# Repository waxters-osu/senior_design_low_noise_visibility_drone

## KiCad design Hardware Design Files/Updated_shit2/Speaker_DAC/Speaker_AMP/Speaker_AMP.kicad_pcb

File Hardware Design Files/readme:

This folder is for all hardware design files.

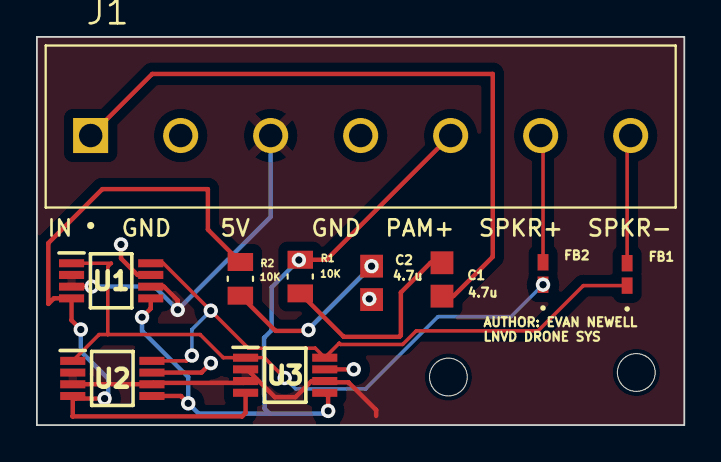
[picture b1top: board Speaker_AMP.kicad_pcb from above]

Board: 2 copper layers, 36.0 x 21.6 mm, 12 parts (0 on the bottom side), 11 nets.

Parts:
C1, C2: 4.7u; Cap0805
FB1, FB2: FerriteBead; IND_BLM15_0402_MUR-M
H1, H2: MountingHole; MountingHole_2.1mm
J1: IN GND 5V GND PAM+ SPKR+ SPKR-; CUI_TB001-500-07BE
R1, R2: 10K; RESC2012X60N
U1, U2, U3: PAM8304; SOP65P490X110-8N

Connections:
/5V: J1.3, U1.2 (PVDD), U1.3 (VDD), U1.6 (SD_N), U2.2 (PVDD), U2.3 (VDD), U2.6 (SD_N), U3.2 (PVDD), U3.3 (VDD), U3.6 (SD_N)
/PAM_NEG: R2.2, U1.4 (IN-), U2.4 (IN-), U3.4 (IN-)
/PAM_O+: FB2.1, U1.1 (OUT+), U2.1 (OUT+), U3.1 (OUT+)
/PAM_O-: FB1.1, U1.8 (OUT-), U2.8 (OUT-), U3.8 (OUT-)
/PAM_POS: J1.5, R1.2, U1.5 (IN+), U2.5 (IN+), U3.5 (IN+)
/SNGL_IN: C1.1, J1.1
/SPEAKER+: FB2.2, J1.6
/SPEAKER-: FB1.2, J1.7
GND: C2.1, J1.2, J1.4, U1.7 (GND), U2.7 (GND), U3.7 (GND)
unnamed: C1.2, R1.1
unnamed: C2.2, R2.1

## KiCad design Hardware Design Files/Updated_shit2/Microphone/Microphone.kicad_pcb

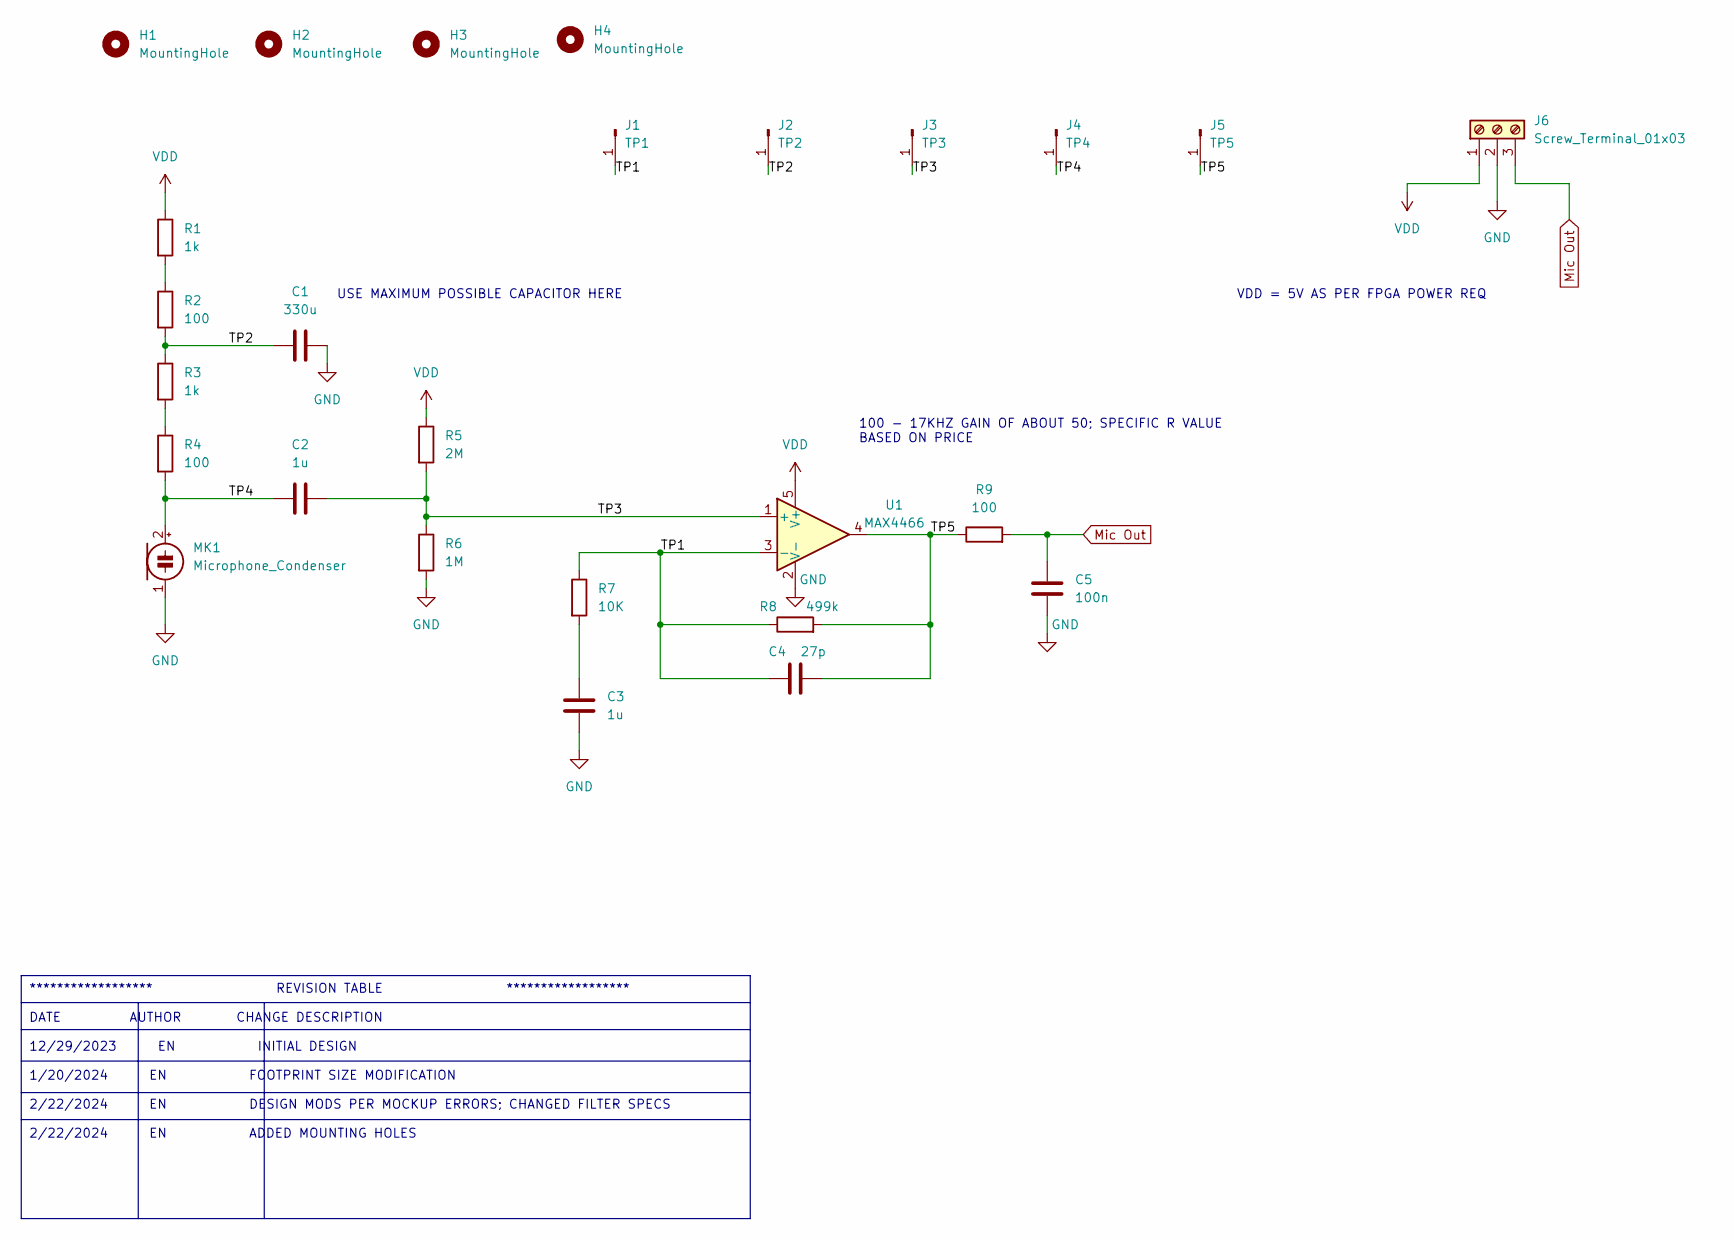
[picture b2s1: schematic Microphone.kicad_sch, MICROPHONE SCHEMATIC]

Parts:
C1: 330u; CAPC3225X280N; Digikey Part # GRM32EC80E337ME05K
C2, C3: 1u; Cap0805; Digikey Part # CL21B105KAFNNNE
C4: 27p; Cap0805; Digikey Part # C0805C270K5GAC7800
C5: 100n; Cap0805; Digikey Part # CC0805KRX7R9BB104
H1, H2, H3, H4: MountingHole; MountingHole_3mm
J1: TP1; ADAM-TECH_PH1-01-UA; Digikey Part # PH1-01-UA
J2: TP2; ADAM-TECH_PH1-01-UA; Digikey Part # PH1-01-UA
J3: TP3; ADAM-TECH_PH1-01-UA; Digikey Part # PH1-01-UA
J4: TP4; ADAM-TECH_PH1-01-UA; Digikey Part # PH1-01-UA
J5: TP5; ADAM-TECH_PH1-01-UA; Digikey Part # PH1-01-UA
J6: Screw_Terminal_01x03; CONN_1984976_PXC; Digikey Part # 1984976
MK1: Microphone_Condenser; CMA_CUI_9P7X9P7_CUD; Digikey Part # CMA-6524PF
R1, R3: 1k; RESC2012X60N; Digikey Part # RMCF0805FT1K00
R2, R4, R9: 100; RESC2012X60N; Digikey Part # RC0805FR-07100RL
R5: 2M; RESC2012X60N; Digikey Part # CRCW08052M00FKECC
R6: 1M; RESC2012X60N; Digikey Part # RMCF0805FG1M00
R7: 10K; RESC2012X60N; Digikey Part # RMCF0805FT10K0
R8: 499k; RESC2012X60N; Digikey Part # CR0805-FX-4993ELF
U1: MAX4466; Mic_Op_Amp; Digikey Part # MAX4466EXK+T

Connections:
/TP1: C4.1, J1.1, R7.1, R8.1, U1.3 (-)
/TP2: C1.1, J2.1, R2.2, R3.1
/TP3: C2.2, J3.1, R5.2, R6.1, U1.1 (+)
/TP4: C2.1, J4.1, MK1.2 (+), R4.2
/TP5: C4.2, J5.1, R8.2, R9.1, U1.4
GND: C1.2, C3.2, C5.2, J6.2, MK1.1 (-), R6.2, U1.2 (V-)
Mic Out: C5.1, J6.3, R9.2
unnamed: C3.1, R7.2
unnamed: R1.2, R2.1
unnamed: R3.2, R4.1
VDD: J6.1, R1.1, R5.1, U1.5 (V+)

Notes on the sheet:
****************** REVISION TABLE ****************** DATE AUTHOR CHANGE DESCRIPTION 12/29/2023 EN INITIAL DESIGN 1/20/2024 EN FOOTPRINT SIZE MODIFICATION 2/22/2024 EN DESIGN MODS PER MOCKUP ERRORS; CHANGED FILTER SPECS 2/22/2024 EN ADDED MOUNTING HOLES
VDD = 5V AS PER FPGA POWER REQ
100 - 17KHZ GAIN OF ABOUT 50; SPECIFIC R VALUE BASED ON PRICE
USE MAXIMUM POSSIBLE CAPACITOR HERE

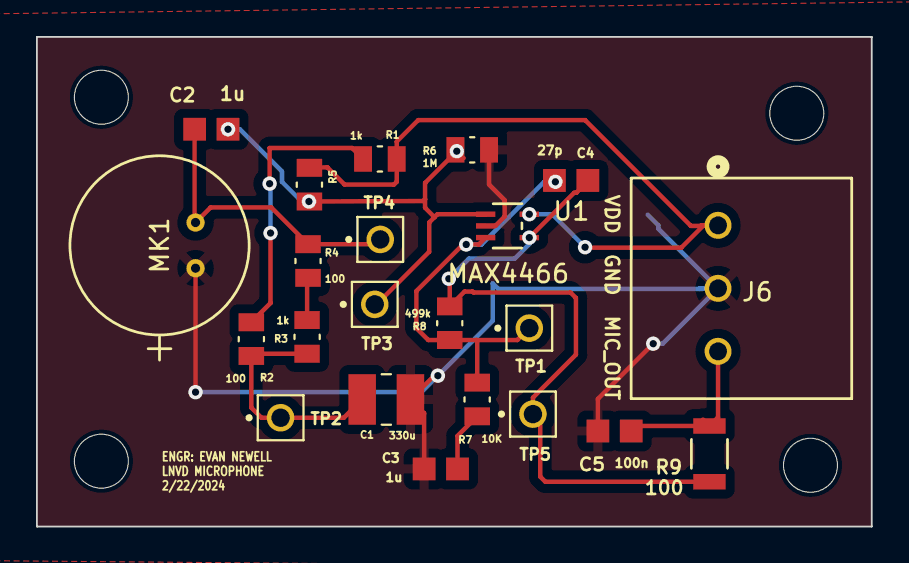
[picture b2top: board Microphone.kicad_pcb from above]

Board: 2 copper layers, 46.4 x 27.2 mm, 26 parts (0 on the bottom side), 11 nets.

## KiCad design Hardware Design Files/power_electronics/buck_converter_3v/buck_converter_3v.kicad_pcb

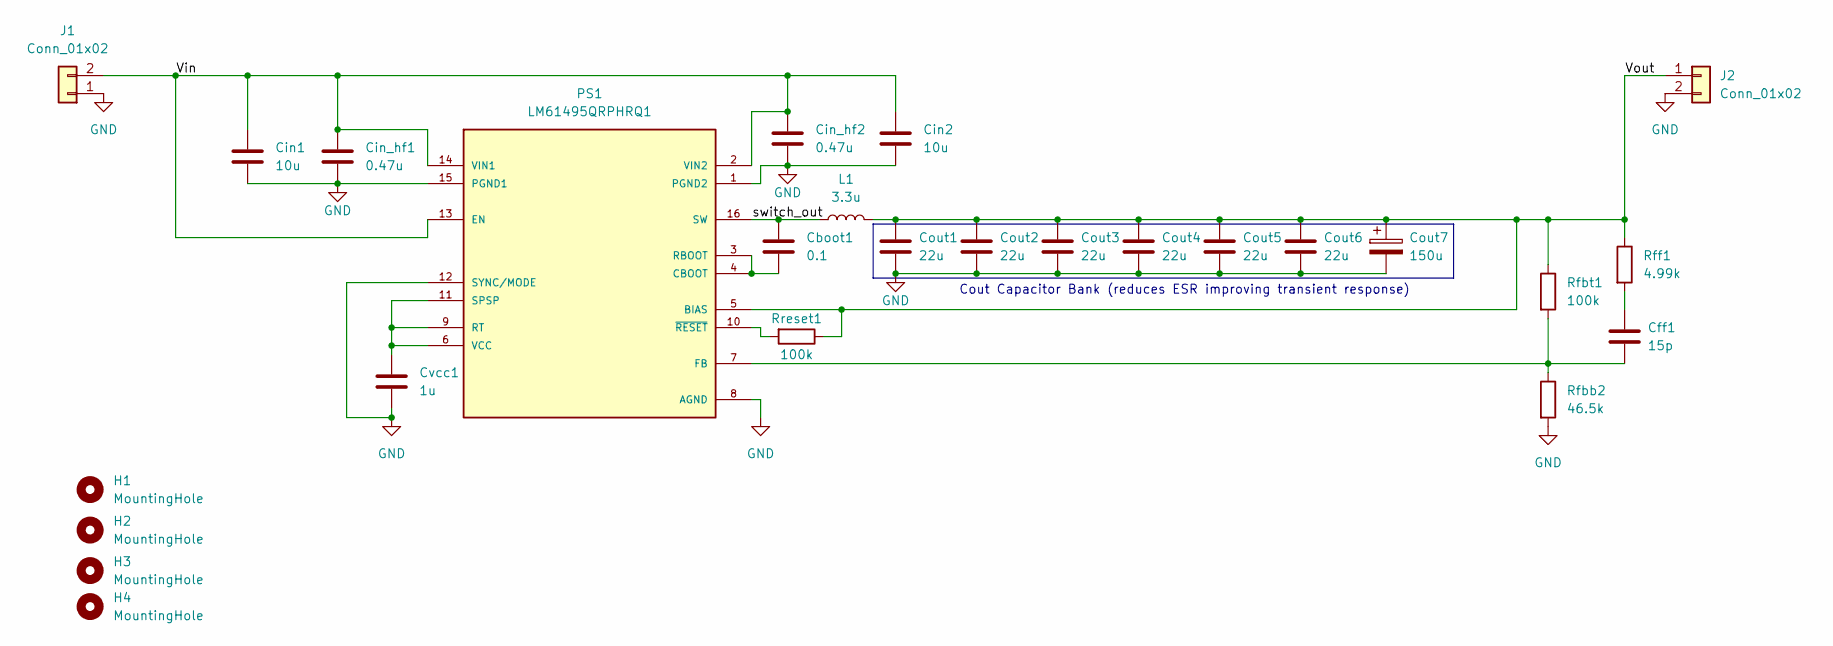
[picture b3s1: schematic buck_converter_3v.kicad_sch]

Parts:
Cboot1: 0.1; C_0805_2012Metric; Digikey PN CL21B104KACNNNC
Cff1: 15p; C_0805_2012Metric; Digikey PN CC0805JRNPO9BN150
Cin1, Cin2: 10u; C_1206_3216Metric; Digikey PN CL31B106KBHNNNE
Cin_hf1, Cin_hf2: 0.47u; C_0603_1608Metric; Digikey PN UMK107B7474KA-TR
Cout1, Cout2, Cout3, Cout4, Cout5, Cout6: 22u; C_0805_2012Metric; Digikey PN CL21A226MQQNNNE
Cout7: 150u; CP_Radial_D5.0mm_P2.00mm; DigikeyPN 860020272007
Cvcc1: 1u; C_0805_2012Metric; Digikey PN CL21B105KAFNNNE
H1, H2, H3, H4: MountingHole; MountingHole_2.5mm_Pad
J1, J2: Conn_01x02; 2-terminal-screw-connector-691137710002; Digikey PN 691137710002
L1: 3.3u; TMPC 1004H-3R3MG-D; Digikey PN TMPC 1004H-3R3MG-D
PS1: LM61495QRPHRQ1; CONV_LM61495QRPHRQ1; PARTREV 08/2018; Digikey PN LM61495QRPHRQ1
Rfbb2: 46.5k; R_0805_2012Metric; Digikey PN ERA-6AEB4642V
Rfbt1: 100k; R_0805_2012Metric; Digikey PN ERA-6AEB104V
Rff1: 4.99k; R_0805_2012Metric; Digikey PN ERA-6AEB4991V
Rreset1: 100k; R_0805_2012Metric; Digikey PN ERA-6AEB104V

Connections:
/Vin: Cin1.1, Cin2.1, Cin_hf1.1, Cin_hf2.1, J1.2, PS1.2 (VIN2), PS1.13 (EN), PS1.14 (VIN1)
/Vout: Cout1.1, Cout2.1, Cout3.1, Cout4.1, Cout5.1, Cout6.1, Cout7.1, J2.1, L1.2, PS1.5 (BIAS), Rfbt1.1, Rff1.1, Rreset1.1
/switch_out: Cboot1.1, L1.1, PS1.16 (SW)
GND: Cin1.2, Cin2.2, Cin_hf1.2, Cin_hf2.2, Cout1.2, Cout2.2, Cout3.2, Cout4.2, Cout5.2, Cout6.2, Cout7.2, Cvcc1.1, J1.1, J2.2, PS1.1 (PGND2), PS1.8 (AGND), PS1.12 (SYNC/MODE), PS1.15 (PGND1), Rfbb2.2; also elsewhere on the board
unnamed: Cff1.1, Rff1.2
unnamed: Cboot1.2, PS1.3 (RBOOT), PS1.4 (CBOOT)
unnamed 6: Cff1.2, PS1.7 (FB), Rfbb2.1, Rfbt1.2; also elsewhere on the board
unnamed: Cvcc1.2, PS1.6 (VCC), PS1.9 (RT), PS1.11 (SPSP)
unnamed: PS1.10 (~RESET), Rreset1.2

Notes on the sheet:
Cout Capacitor Bank (reduces ESR improving transient response)

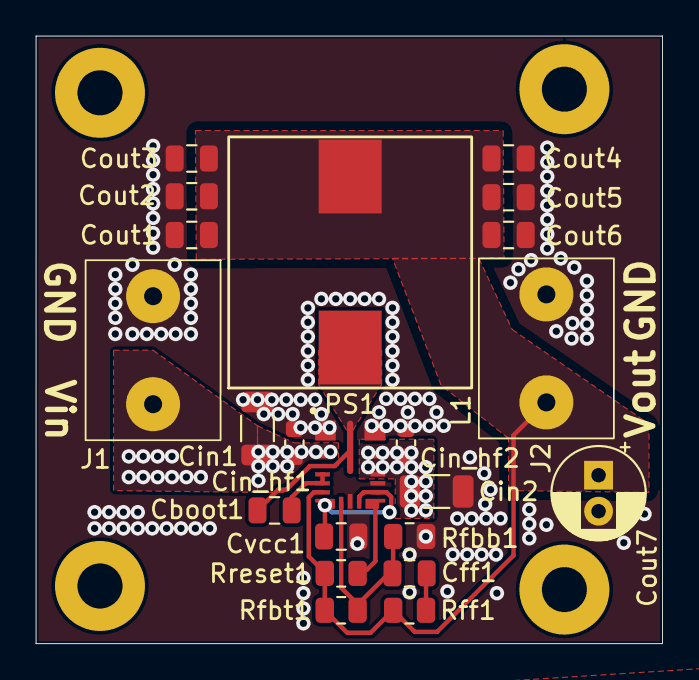
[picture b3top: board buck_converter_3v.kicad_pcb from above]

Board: 2 copper layers, 34.8 x 33.8 mm, 26 parts (0 on the bottom side), 9 nets.

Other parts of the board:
Rfbb1: 25.5k; R_0805_2012Metric

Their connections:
GND: Rfbb1.2; also elsewhere on the board
unnamed 6: Rfbb1.1; also elsewhere on the board

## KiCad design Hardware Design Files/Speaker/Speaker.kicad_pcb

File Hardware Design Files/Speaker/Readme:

This folder contains all hardware files pertaining to the speaker

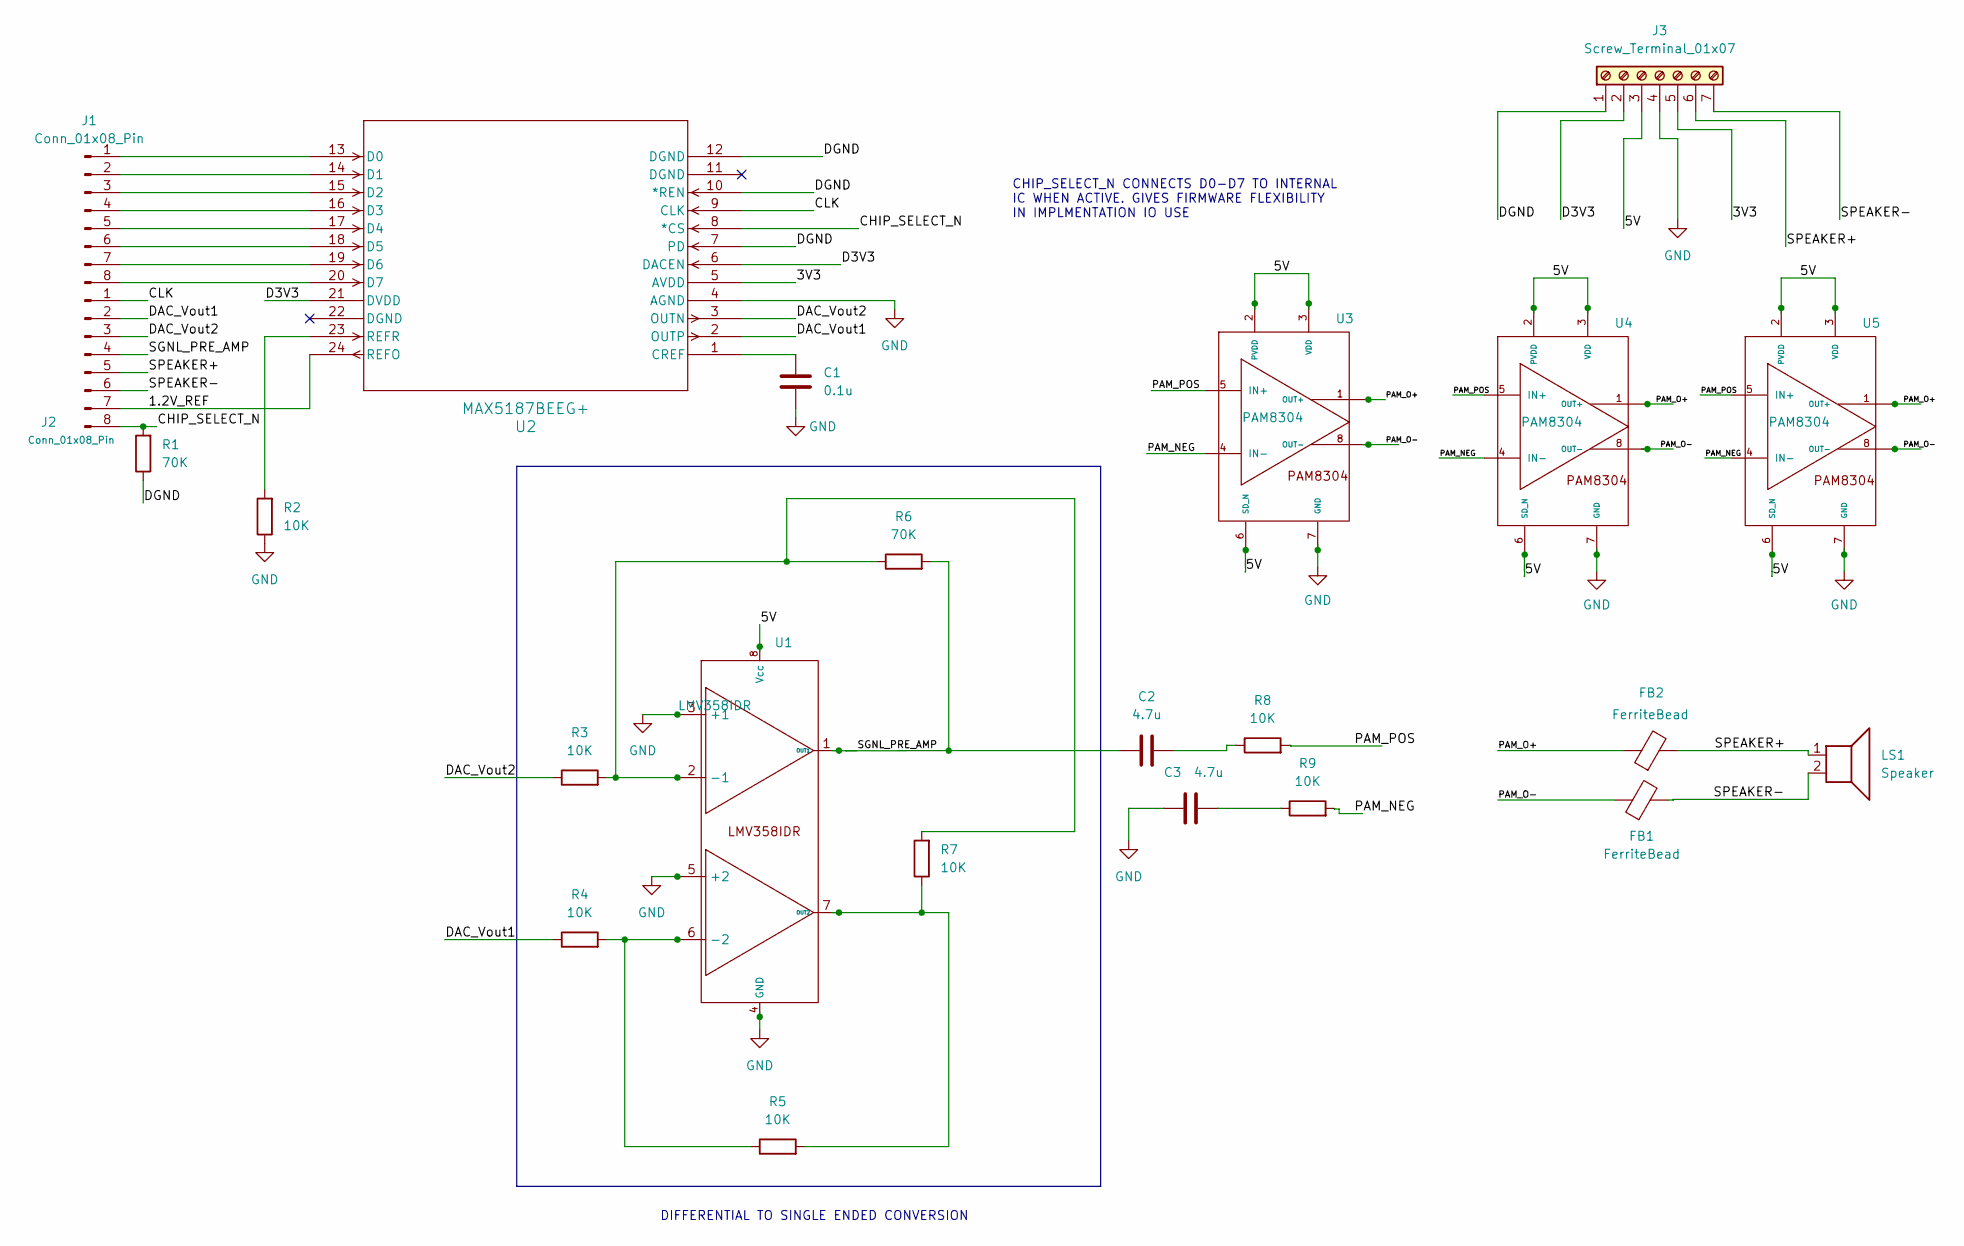
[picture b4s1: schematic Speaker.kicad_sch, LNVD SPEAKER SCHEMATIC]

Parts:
C1: 0.1u; CAP_CL10_SAM-M; DIGIKEY PART # GRM033C81E104ME14D
C2, C3: 4.7u; CAP_CL10_SAM-M; DIGIKEY PART # CL10A475KQ8NNWC
FB1, FB2: FerriteBead; IND_BLM15_0402_MUR-M; DIGIKEY PART # BLM15AG121SN1D
J1, J2: Conn_01x08_Pin; CONN_1945151_PXC; DIGIKEY PART # 1945151
J3: Screw_Terminal_01x07; CUI_TB001-500-07BE; DIGIKEY PART # TB001-500-07BE
LS1: Speaker; DIGIKEY PART # CDS-4224-84SP
R1, R6: 70K; RESC2012X60N; DIGIKEY PART # ERJ-1GNF6982C
R2, R3, R4, R5, R7, R8, R9: 10K; RESC2012X60N; DIGIKEY PART # RMCF0805FT10K0
U1: LMV358IDR; D8-M; DIGIKEY PART # LMV358IDR
U2: MAX5187BEEG+; 21-0055H_24-M; DIGIKEY PART # MAX5187BEEG+
U3, U4, U5: PAM8304; SOP65P490X110-8N; DIGIKEY PART # PAM8304ASR

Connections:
/1.2V_REF: J2.7, U2.24 (REFO)
/3V3: J3.5, U2.5 (AVDD)
/5V: J3.3, U1.8 (Vcc), U3.2 (PVDD), U3.3 (VDD), U3.6 (SD_N), U4.2 (PVDD), U4.3 (VDD), U4.6 (SD_N), U5.2 (PVDD), U5.3 (VDD), U5.6 (SD_N)
/CHIP_SELECT_N: J2.8, R1.2, U2.8 (*CS)
/CLK: J2.1, U2.9 (CLK)
/D3V3: J3.2, U2.6 (DACEN), U2.21 (DVDD)
/DAC_Vout1: J2.2, R4.1, U2.2 (OUTP)
/DAC_Vout2: J2.3, R3.1, U2.3 (OUTN)
/DGND: J3.1, R1.1, U2.7 (PD), U2.10 (*REN), U2.12 (DGND)
/PAM_NEG: R9.2, U3.4 (IN-), U4.4 (IN-), U5.4 (IN-)
/PAM_O+: FB2.1, U3.1 (OUT+), U4.1 (OUT+), U5.1 (OUT+)
/PAM_O-: FB1.1, U3.8 (OUT-), U4.8 (OUT-), U5.8 (OUT-)
/PAM_POS: R8.2, U3.5 (IN+), U4.5 (IN+), U5.5 (IN+)
/SGNL_PRE_AMP: C2.1, J2.4, R6.2, U1.1 (OUT1)
/SPEAKER+: FB2.2, J2.5, J3.6, LS1.1
/SPEAKER-: FB1.2, J2.6, J3.7, LS1.2
GND: C1.2, C3.1, J3.4, R2.1, U1.3 (+1), U1.4 (GND), U1.5 (+2), U2.4 (AGND), U3.7 (GND), U4.7 (GND), U5.7 (GND)
unnamed: C2.2, R8.1
unnamed: C3.2, R9.1
unnamed: J1.1, U2.13 (D0)
unnamed: J1.2, U2.14 (D1)
unnamed: J1.3, U2.15 (D2)
unnamed: J1.4, U2.16 (D3)
unnamed: J1.5, U2.17 (D4)
unnamed: J1.6, U2.18 (D5)
unnamed: J1.7, U2.19 (D6)
unnamed: J1.8, U2.20 (D7)
unnamed: R3.2, R6.1, R7.2, U1.2 (-1)
unnamed: R4.2, R5.1, U1.6 (-2)
unnamed: R5.2, R7.1, U1.7 (OUT2)
unnamed: C1.1, U2.1 (CREF)
unnamed: R2.2, U2.23 (REFR)

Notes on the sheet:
DIFFERENTIAL TO SINGLE ENDED CONVERSION
CHIP_SELECT_N CONNECTS D0-D7 TO INTERNAL IC WHEN ACTIVE. GIVES FIRMWARE FLEXIBILITY IN IMPLMENTATION IO USE

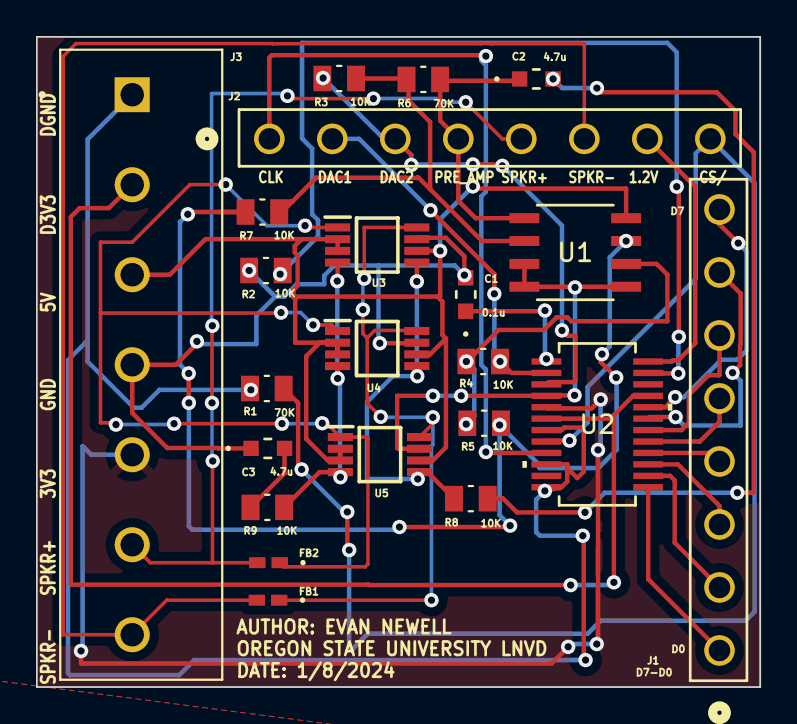
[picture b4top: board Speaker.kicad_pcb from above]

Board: 2 copper layers, 40.2 x 36.1 mm, 22 parts (0 on the bottom side), 32 nets.

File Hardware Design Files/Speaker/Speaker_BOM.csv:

"Reference","Value","Footprint","Datasheet","DIGIKEY PART #","PRICE","Qty"
"C1","0.1u","Footprints:CAP_CL10_SAM-M","~https://search.murata.co.jp/Ceramy/image/img/A01X/G101/ENG/G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","GRM033C81E104ME14D","$0.10","1"
"C2, C3","4.7u","Footprints:CAP_CL10_SAM-M","~https://mm.digikey.com/Volume0/opasdata/d220001/medias/docus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","CL10A475KQ8NNWC","$0.10","2"
"FB1, FB2","FerriteBead","Footprints:IND_BLM15_0402_MUR-M","~https://www.murata.com/en-us/products/productdata/8796740059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","BLM15AG121SN1D","$0.10","2"
"J1, J2","Conn_01x08_Pin","Footprints:CONN_1945151_PXC","~https://mm.digikey.com/Volume0/opasdata/d220001/medias/docus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","1945151","$0.85","2"
"J3","Screw_Terminal_01x07","Footprints:CUI_TB001-500-07BE","~https://www.cuidevices.com/product/resource/tb001-500.pdf","TB001-500-07BE","$0.96","1"
"LS1","Speaker","","~https://www.cuidevices.com/product/resource/cds-4224-84sp.pdf","CDS-4224-84SP","$7.82","1"
"R1-R5, R7-R9","10K","Footprints:RESC2012X60N","~https://www.seielect.com/catalog/sei-rmcf_rmcp.pdf","RMCF0805FT10K0","$0.10","8"
"R6","70K","Footprints:RESC2012X60N","https://industrial.panasonic.com/cdbs/www-data/pdf/RDA0000/A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","ERJ-1GNF6982C","$0.10","1"
"U1","LMV358IDR","Footprints:D8-M","https://rocelec.widen.net/view/pdf/hsbslfymvc/slos263w.pdf?t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","LMV358IDR","$0.36","1"
"U2","MAX5187BEEG+","Footprints:21-0055H_24-M","https://www.analog.com/media/en/technical-documentation/data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","MAX5187BEEG+","$7.57","1"
"U3-U5","PAM8304","Footprints:SOP65P490X110-8N","https://www.diodes.com/assets/Datasheets/PAM8304.pdf","PAM8304ASR","$0.70","3"

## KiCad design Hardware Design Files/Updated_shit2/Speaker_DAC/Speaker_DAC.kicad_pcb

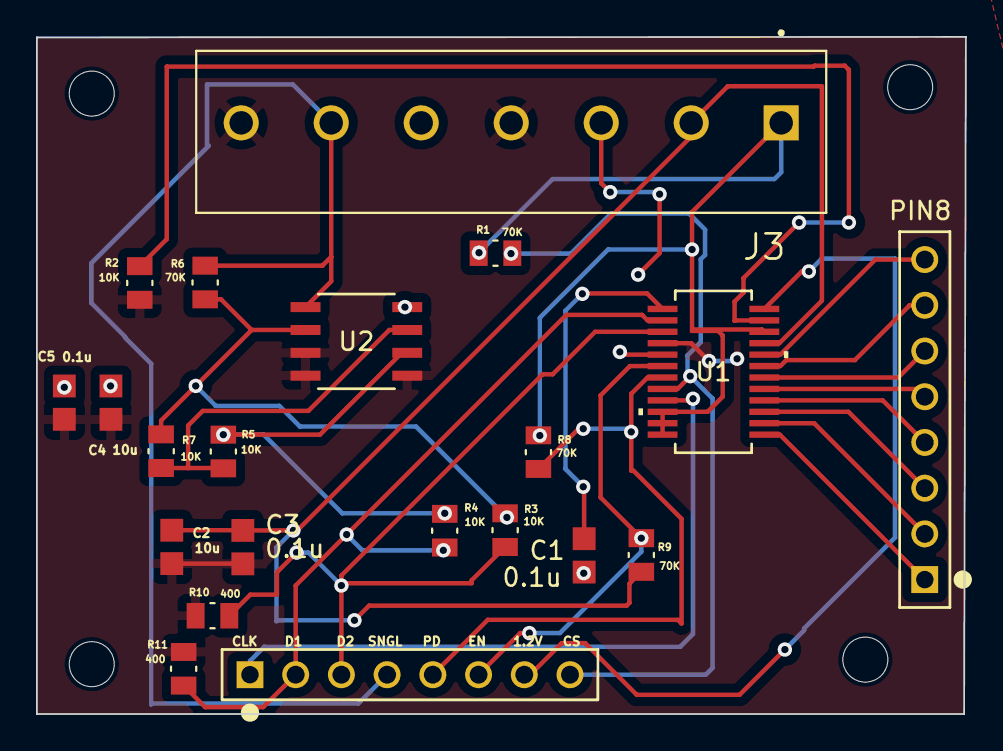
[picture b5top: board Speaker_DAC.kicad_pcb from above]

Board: 2 copper layers, 51.6 x 37.6 mm, 25 parts (0 on the bottom side), 26 nets.

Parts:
C1, C3, C5: 0.1u; Cap0805
C2, C4: 10u; Cap0805
CLK    D1     D2  SNGL   PD    EN    1.2V   CS: Conn_01x08_Pin; CONN8_PREC008SAAN-RC_SUL
H1, H2, H3, H4: MountingHole; MountingHole_2.5mm
J3: Screw_Terminal_01x07; CUI_TB001-500-07BE
PIN8: Conn_01x08_Pin; CONN8_PREC008SAAN-RC_SUL
R1, R6, R8, R9: 70K; RESC2012X60N
R2, R3, R4, R5, R7: 10K; RESC2012X60N
R10, R11: 400; RESC2012X60N
U1: MAX5187BEEG+; 21-0055H_24-M
U2: LMV358IDR; D8-M

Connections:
/1.2V_REF: CLK D1 D2 SNGL PD EN 1.2V CS.7, U1.24 (REFO)
/3V3: C1.2, J3.3, U1.5 (AVDD)
/5V: C4.1, C5.1, J3.5, U2.8 (Vcc)
/CHIP_SELECT_N: CLK D1 D2 SNGL PD EN 1.2V CS.8, R1.2, U1.8 (*CS)
/CLK: CLK D1 D2 SNGL PD EN 1.2V CS.1, U1.9 (CLK)
/D3V3: C2.1, C3.1, J3.2, R9.2, U1.21 (DVDD)
/DACEN: CLK D1 D2 SNGL PD EN 1.2V CS.6, R9.1, U1.6 (DACEN)
/DAC_Vout1: CLK D1 D2 SNGL PD EN 1.2V CS.2, R4.1, R11.2, U1.2 (OUTP)
/DAC_Vout2: CLK D1 D2 SNGL PD EN 1.2V CS.3, R3.1, R10.2, U1.3 (OUTN)
/DGND: J3.1, R1.1, R8.2, U1.10 (*REN), U1.11 (DGND), U1.12 (DGND), U1.22 (DGND)
/PD: CLK D1 D2 SNGL PD EN 1.2V CS.5, R8.1, U1.7 (PD)
GND: C2.2, C3.2, C4.2, C5.2, J3.4, J3.7, R2.1, R10.1, R11.1, U1.4 (AGND), U2.3 (+1), U2.4 (GND), U2.5 (+2)
unnamed: PIN8.1, U1.13 (D0)
unnamed: PIN8.2, U1.14 (D1)
unnamed: PIN8.3, U1.15 (D2)
unnamed: PIN8.4, U1.16 (D3)
unnamed: PIN8.5, U1.17 (D4)
unnamed: PIN8.6, U1.18 (D5)
unnamed: PIN8.7, U1.19 (D6)
unnamed: PIN8.8, U1.20 (D7)
unnamed: C1.1, U1.1 (CREF)
unnamed: R2.2, U1.23 (REFR)
unnamed: R3.2, R6.1, R7.2, U2.2 (-1)
unnamed: R4.2, R5.1, U2.6 (-2)
unnamed: R5.2, R7.1, U2.7 (OUT2)
SNGL_OUT: CLK D1 D2 SNGL PD EN 1.2V CS.4, J3.6, R6.2, U2.1 (OUT1)

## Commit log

2023-10-16 Initial Overleaf Import
2023-10-16 exp: check other files appear in overleaf
2023-10-16 put the title on separate page
2023-10-16 Updates from Overleaf
2023-10-16 docs: remove project-specific content from which this template is from
2023-12-26 project document non-atomic commit: - commit all changes up through winter break. - restructure document directory so monorepo can be good.
2023-12-26 feat: record audio using mic
2023-12-27 feat: plot proportional PSD using Welch's Method
2023-12-27 chore: add soundfile module as a dependency
2023-12-27 refactor: convert recording, play, and estimate psd into functions
2023-12-27 feat: add save and load recording file functions
2023-12-27 feat: make cli for working with single recording
2023-12-27 feat: add ambient and device active recording instead of single recording
2023-12-27 feat: add graph difference psd for active minus background spectrum
2023-12-30 Add files via upload
    INITIAL MICROPHONE DESIGN
2023-12-30 Add files via upload
    PCB Mock 1
2023-12-30 Add files via upload
    Required PCB Footprint Files for Microphone
2023-12-30 Create readme
    Create readme and folder for Hardware Design files
2023-12-30 Add files via upload
    Kicad design files
2023-12-30 Adjusted Edge cuts
    Adjusted Edge cuts and excluded DRC
2023-12-30 fix: ignore DRC overlap soldermask 0603 footprint
2023-12-30 chore(gitignore): add gitignore for kicad files in hw design
2023-12-30 Updated footprint library
    Made footprint library the appropriate format such that pulling files does not require as much work for a clean DRC
2023-12-30 Returned PCB Files
    Previous commit accidentally ommitted footprint files. This change rectifies this
2024-01-03 fix(audio_spectral_script): change welch's parameters to reduce spectral leakage
2024-01-03 docs(audio_spectral_script): fix install/run instructions
2024-01-03 Adjusted Load Command
    Built in error handling of loading an improper audio file;\n Now it can handle bad files without failing
2024-01-03 fix(audio_spectral_script): make recording last intended duration
2024-01-09 Add files via upload
    Added kicad files
2024-01-09 Add files via upload
    Symbol file library
    custom symbols used in schematic
2024-01-09 added all footprints and symbols in native format
    reformatted everything such that it wasn't brain dead
2024-01-09 Add files via upload
    Added BOM
2024-01-09 added label to pcb
2024-01-09 added pdf schematic +
    pdf schematic, added change table, adjusted minor silk screen error; Note that DRC will yield 2 errors which can be ignored safely
2024-01-09 changed R1
    changed from 10k to 70k such that chip select current ~5ua
2024-01-23 chore(audio_power_spectrum_script): ignore .wav and .png files
2024-01-27 feat(5v_converter): create schematic for datasheets application
2024-01-28 feat: apply application ref values to components for block validation doc
2024-01-31 docs(buck_converter): remove schematic screenshots
2024-01-31 feat(buck_converter_3v): select specific parts on digikey
2024-02-01 chore(git): do not track autosave files
2024-02-01 feat(buck_converter_3v): create PCB
2024-02-01 refactor(buck_converter_3v): apply jlcpcb fab design rules
2024-02-01 feat(buck_converter): unify pcb design, schematic varies by resistor value, add mounting holes
2024-03-02 New pcb's as of 3/2
2024-04-05 fuck you silas
2024-04-06 fuck ya mofo this was done by me silas
    functioning ADC in verilog 22.1
2024-04-07 Full ADC system
    Functioning ADC module for final dez + testbench
2024-04-07 Functioning Inverter
    Full inverter module and testbench
2024-04-07 Functioning Noise Inverter
    Functioning Noise inverter and testbench ... literally something that works
2024-04-20 code for testing screen
